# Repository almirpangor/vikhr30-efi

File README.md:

# Вихрь-30 EFI

Блок управления впрыском и зажиганием для лодочного мотора «Вихрь-30» на STM32F103C6T6 (Blue Pill):
программа настройки, прошивка, схема и печатная плата.

| Папка | Что внутри |
|---|---|
| `app/` | Программа настройки 2.0 (TypeScript, React, свой WebGL-движок). `app/desktop/` — оболочка настольного приложения (Electron). Сборка: `node build.mjs`, тесты ядра: `npm test`. |
| `firmware/` | Прошивка v0.9 (исправленная) и v0.8 (для отката), симулятор и тесты на хосте, готовые HEX/BIN в `firmware/release/`. Читать `firmware/README_RU.md`. |
| `pcb/` | Печатная плата rev A: генератор, Gerber и сверловка в `pcb/out/`, файл KiCad, сборочные рисунки, перечень. Читать `pcb/out/README_RU.md`. |
| `release/` | Собранная программа одним HTML-файлом (Chrome/Edge). Установщик для Windows — в разделе Releases. |

## Состояние

Проверено без железа: 24 автотеста ядра программы, 48 проверок прошивки на симуляторе, соответствие Gerber схеме по всем 63 цепям.

**Не проверено на железе:** прошивка v0.9 на настоящем контроллере, программа с настоящим COM-портом,
установщик на Windows, плата (не изготавливалась, файл KiCad в KiCad не открывался), схема из новых деталей.
Перед заказом платы — список «Сверить перед заказом» в `pcb/out/README_RU.md`.

Первые включения — на стенде, с предохранителем и ограничением тока, без топлива. Цепи катушек — до 400 В.

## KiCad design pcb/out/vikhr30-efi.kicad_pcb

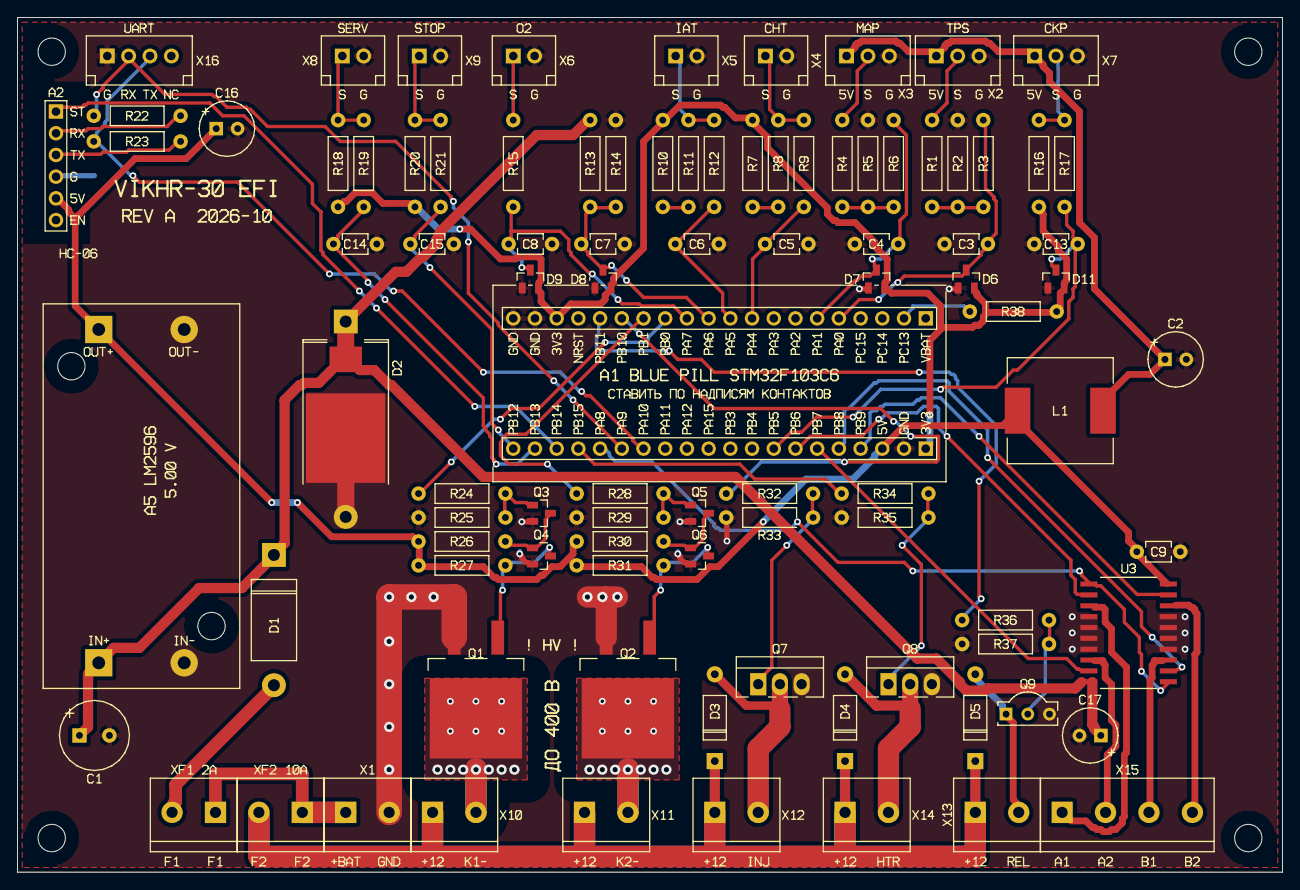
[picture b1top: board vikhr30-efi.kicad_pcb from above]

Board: 2 copper layers, 148.0 x 100.0 mm, 98 parts (0 on the bottom side), 63 nets.

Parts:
A1: Blue Pill STM32F103C6T6; BLUEPILL_2x20
A2: HC-06; HDR_1x6
A5: LM2596S, 5,00 В; LM2596_MODULE
C1: 470 мкФ × 25 В; CP_D8_P3.5
C2, C16, C17: 47 мкФ × 63 В; CP_D6.3_P2.5
C3, C4, C5, C6, C7, C8, C9: 0,1 мкФ; C_DISC_5.08
C13, C14, C15: 1 нФ; C_DISC_5.08
D1: SR560; DO-201AD_15.24
D2: SM8S30A; DO-218AB
D3, D4, D5: 1N4007; DO-41_10.16
D6, D7, D8, D9, D11: BAR43S; SOT-23
H1, H2, H3, H4: M3; MountingHole_3.2mm_M3
L1: 47 мкГн; CDRH125
Q1, Q2: IRGS14C40L; TO-263-2
Q3, Q4, Q5, Q6: AO3400A; SOT-23
Q7, Q8: IRLZ44N; TO-220_V
Q9: BC547C; TO-92
R1, R4, R14, R15, R18, R20, R25, R29, R37, R38: 10 кОм; R_AXIAL_10.16
R2, R5: 20 кОм; R_AXIAL_10.16
R3, R6, R9, R12, R17, R19, R21, R22, R23, R26, R30, R36: 1 кОм; R_AXIAL_10.16
R7, R10: 2,4 кОм; R_AXIAL_10.16
R8, R11: 91 Ом; R_AXIAL_10.16
R13: 47 кОм; R_AXIAL_10.16
R16: 4,7 кОм; R_AXIAL_10.16
R24, R28: 330 Ом; R_AXIAL_10.16
R27, R31: 470 Ом; R_AXIAL_10.16
R32, R34: 100 Ом; R_AXIAL_10.16
R33, R35: 100 кОм; R_AXIAL_10.16
U3: L293DD; SO-20W
X1, X10, X11, X12, X13, X14: Клеммник 2 конт.; TERM_5.08_2
X2, X3, X7: JST XH 3 конт.; JST_XH_3
X4, X5, X6, X8, X9: JST XH 2 конт.; JST_XH_2
X15: JST XH 4 конт.; TERM_5.08_4
X16: JST XH 4 конт. (USB-UART A3); JST_XH_4
XF1: Клеммник 2 конт. к держателю F1 (2 А); TERM_5.08_2R
XF2: Клеммник 2 конт. к держателю F2 (10 А); TERM_5.08_2R

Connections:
+3V3: A1.JL18, A1.JR1, D6.2, D7.2, D8.2, D9.2, D11.2, R7.1, R10.1, R16.1, R18.1, R20.1, R38.1
+5V_ECU: A1.JR3, A2.5, A5.3, C9.1, C16.1, L1.1, R26.1, R27.1, R30.1, R31.1, U3.20
+5V_SENS: C2.1, L1.2, X2.1, X3.1, X7.1
+12V_F2: D3.1, D4.1, D5.1, X10.1, X11.1, X12.1, X13.1, X14.1, XF2.2
+12V_PROT: A5.1, C1.1, C17.1, D1.1, D2.1, R13.1, U3.10
BAT+: X1.1, XF1.1, XF2.1
COIL1-: Q1.2, X10.2
COIL2-: Q2.2, X11.2
GND: A1.JL19, A1.JL20, A1.JR2, A2.4, A5.2, A5.4, C1.2, C2.2, C3.2, C4.2, C5.2, C6.2, C7.2, C8.2, C9.2, C13.2, C14.2, C15.2, C16.2, C17.2, D2.2, D6.1, D7.1, D8.1, D9.1, D11.1, Q1.3, Q2.3, Q3.2, Q4.2, Q5.2, Q6.2, Q7.3, Q8.3, Q9.3, R2.2, R5.2, R14.2, R25.2, R29.2, R33.2, R35.2, R37.2, U3.4, U3.5, U3.6, U3.7, U3.14, U3.15, U3.16, U3.17, X1.2, X2.3, X3.3, X4.2, X5.2, X6.2, X7.3, X8.2, X9.2, X16.1
HEATER-: D4.2, Q8.2, X14.2
IAC_A1: U3.3, X15.1
IAC_A2: U3.8, X15.2
IAC_B1: U3.13, X15.3
IAC_B2: U3.18, X15.4
IGN1_GATE: Q1.1, Q4.3, R27.2
IGN2_GATE: Q2.1, Q6.3, R31.2
INJ-: D3.2, Q7.2, X12.2
MAP_SIG: R4.1, X3.2
N_D1_A: D1.2, XF1.2
N_Q3_1: Q3.1, R24.2, R25.1
N_Q3_3: Q3.3, Q4.1, R26.2
N_Q5_1: Q5.1, R28.2, R29.1
N_Q5_3: Q5.3, Q6.1, R30.2
N_Q7_1: Q7.1, R32.2, R33.1
N_Q8_1: Q8.1, R34.2, R35.1
N_Q9_2: Q9.2, R36.2, R37.1
N_R1_2: R1.2, R2.1, R3.1
N_R4_2: R4.2, R5.1, R6.1
N_R7_2: R7.2, R8.1
N_R10_2: R10.2, R11.1
PA0: A1.JL5, C3.1, D6.3, R3.2
PA1: A1.JL6, C4.1, D7.3, R6.2
PA4: A1.JL9, C5.1, R9.2
PA4_X4: R8.2, R9.1, X4.1
PA5: A1.JL10, C6.1, R12.2
PA5_X5: R11.2, R12.1, X5.1
PA6: A1.JL11, C7.1, D8.3, R13.2, R14.1
PA7: A1.JL12, C8.1, D9.3, R15.2
PA7_X6: R15.1, X6.1
PA8: A1.JR16, U3.1, U3.11
PA9: A1.JR15, R22.1, X16.2
PA9_A2: A2.2, R22.2
PA10: A1.JR14, R23.1, X16.3
PA10_A2: A2.3, R23.2
PB0: A1.JL13, R24.1
PB1: A1.JL14, R28.1
PB5: A1.JR8, C13.1, D11.3, R17.2
PB5_X7: R16.2, R17.1, X7.2
PB6: A1.JR7, U3.2
PB7: A1.JR6, U3.9
PB8: A1.JR5, U3.12
PB9: A1.JR4, U3.19
PB10: A1.JL15, R32.1
PB11: A1.JL16, R36.1
PB12: A1.JR20, C15.1, R21.2
PB12_X9: R20.2, R21.1, X9.1
PB13: A1.JR19, C14.1, R19.2
PB13_X8: R18.2, R19.1, X8.1
PB14: A1.JR18, A2.1
PB15: A1.JR17, R34.1
PC13: A1.JL2, R38.2
RELAY-: D5.2, Q9.1, X13.2
TPS_SIG: R1.1, X2.2

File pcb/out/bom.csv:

Обозначение;Номинал / тип;Корпус (посадочное место);Кол-во;Что купить (строка перечня программы);Ссылка магазина
A1;Blue Pill STM32F103C6T6;BLUEPILL_2x20;1;Плата STM32F103C6T6 (Blue Pill HW-267);https://magazin-elektronika.ru/73-84-23
A2;HC-06;HDR_1x6;1;Bluetooth-модуль HC-06;https://magazin-elektronika.ru/78-00-66
A5;LM2596S, 5,00 В;LM2596_MODULE;1;DC-DC модуль LM2596S (4–40 В → 5 В, 2 А);https://magazin-elektronika.ru/78-96-44
C1;470 мкФ × 25 В;CP_D8_P3.5;1;Конденсатор 470 мкФ × 25 В;https://magazin-elektronika.ru/99-01-97
C2, C16, C17;47 мкФ × 63 В;CP_D6.3_P2.5;3;Конденсатор 47 мкФ × 63 В;https://magazin-elektronika.ru/99-02-36
C3, C4, C5, C6, C7, C8, C9;0,1 мкФ;C_DISC_5.08;7;Конденсатор керамический 0,1 мкФ × 50 В;https://magazin-elektronika.ru/99-00-22
C13, C14, C15;1 нФ;C_DISC_5.08;3;Конденсатор керамический 1 нФ × 50 В;
D1;SR560;DO-201AD_15.24;1;Диод Шоттки SR560 (5 А, 60 В);https://magazin-elektronika.ru/99-42-50
D2;SM8S30A;DO-218AB;1;TVS-диод SM8S30A;https://magazin-elektronika.ru/76-06-46
D3, D4, D5;1N4007;DO-41_10.16;3;Диод 1N4007;https://magazin-elektronika.ru/99-43-56
D6, D7, D8, D9, D11;BAR43S;SOT-23;5;Сборка диодов Шоттки BAR43S (SOT-23);https://magazin-elektronika.ru/76-18-88
L1;47 мкГн;CDRH125;1;Дроссель 47 мкГн, 1,8 А (CDRH125);https://magazin-elektronika.ru/75-99-72
Q1, Q2;IRGS14C40L;TO-263-2;2;IGBT зажигания IRGS14C40L (TO-263);https://magazin-elektronika.ru/99-46-03
Q3, Q4, Q5, Q6;AO3400A;SOT-23;4;MOSFET AO3400A (SOT-23);https://magazin-elektronika.ru/73-20-80
Q7, Q8;IRLZ44N;TO-220_V;2;MOSFET IRLZ44N (TO-220);https://magazin-elektronika.ru/99-46-44
Q9;BC547C;TO-92;1;Транзистор BC547C;https://magazin-elektronika.ru/99-52-75
R1, R4, R14, R15, R18, R20, R25, R29, R37, R38;10 кОм;R_AXIAL_10.16;10;Резисторы 0,25 Вт: 91 Ом, 100 Ом, 330 Ом, 470 Ом, 1 кОм, 2,4 кОм, 4,7 кОм, 10 кОм, 20 кОм, 47 кОм, 100 кОм;https://magazin-elektronika.ru/elektronnye-komponenty/rezistory-13
R2, R5;20 кОм;R_AXIAL_10.16;2;Резисторы 0,25 Вт: 91 Ом, 100 Ом, 330 Ом, 470 Ом, 1 кОм, 2,4 кОм, 4,7 кОм, 10 кОм, 20 кОм, 47 кОм, 100 кОм;https://magazin-elektronika.ru/elektronnye-komponenty/rezistory-13
R3, R6, R9, R12, R17, R19, R21, R22, R23, R26, R30, R36;1 кОм;R_AXIAL_10.16;12;Резисторы 0,25 Вт: 91 Ом, 100 Ом, 330 Ом, 470 Ом, 1 кОм, 2,4 кОм, 4,7 кОм, 10 кОм, 20 кОм, 47 кОм, 100 кОм;https://magazin-elektronika.ru/elektronnye-komponenty/rezistory-13
R7, R10;2,4 кОм;R_AXIAL_10.16;2;Резисторы 0,25 Вт: 91 Ом, 100 Ом, 330 Ом, 470 Ом, 1 кОм, 2,4 кОм, 4,7 кОм, 10 кОм, 20 кОм, 47 кОм, 100 кОм;https://magazin-elektronika.ru/elektronnye-komponenty/rezistory-13
R8, R11;91 Ом;R_AXIAL_10.16;2;Резисторы 0,25 Вт: 91 Ом, 100 Ом, 330 Ом, 470 Ом, 1 кОм, 2,4 кОм, 4,7 кОм, 10 кОм, 20 кОм, 47 кОм, 100 кОм;https://magazin-elektronika.ru/elektronnye-komponenty/rezistory-13
R13;47 кОм;R_AXIAL_10.16;1;Резисторы 0,25 Вт: 91 Ом, 100 Ом, 330 Ом, 470 Ом, 1 кОм, 2,4 кОм, 4,7 кОм, 10 кОм, 20 кОм, 47 кОм, 100 кОм;https://magazin-elektronika.ru/elektronnye-komponenty/rezistory-13
R16;4,7 кОм;R_AXIAL_10.16;1;Резисторы 0,25 Вт: 91 Ом, 100 Ом, 330 Ом, 470 Ом, 1 кОм, 2,4 кОм, 4,7 кОм, 10 кОм, 20 кОм, 47 кОм, 100 кОм;https://magazin-elektronika.ru/elektronnye-komponenty/rezistory-13
R24, R28;330 Ом;R_AXIAL_10.16;2;Резисторы 0,25 Вт: 91 Ом, 100 Ом, 330 Ом, 470 Ом, 1 кОм, 2,4 кОм, 4,7 кОм, 10 кОм, 20 кОм, 47 кОм, 100 кОм;https://magazin-elektronika.ru/elektronnye-komponenty/rezistory-13
R27, R31;470 Ом;R_AXIAL_10.16;2;Резисторы 0,25 Вт: 91 Ом, 100 Ом, 330 Ом, 470 Ом, 1 кОм, 2,4 кОм, 4,7 кОм, 10 кОм, 20 кОм, 47 кОм, 100 кОм;https://magazin-elektronika.ru/elektronnye-komponenty/rezistory-13
R32, R34;100 Ом;R_AXIAL_10.16;2;Резисторы 0,25 Вт: 91 Ом, 100 Ом, 330 Ом, 470 Ом, 1 кОм, 2,4 кОм, 4,7 кОм, 10 кОм, 20 кОм, 47 кОм, 100 кОм;https://magazin-elektronika.ru/elektronnye-komponenty/rezistory-13
R33, R35;100 кОм;R_AXIAL_10.16;2;Резисторы 0,25 Вт: 91 Ом, 100 Ом, 330 Ом, 470 Ом, 1 кОм, 2,4 кОм, 4,7 кОм, 10 кОм, 20 кОм, 47 кОм, 100 кОм;https://magazin-elektronika.ru/elektronnye-komponenty/rezistory-13
U3;L293DD;SO-20W;1;Драйвер L293DD (SO-20);https://magazin-elektronika.ru/99-86-61
X1, X10, X11, X12, X13, X14;Клеммник 2 конт.;TERM_5.08_2;6;Клеммник разъёмный 5,08 мм 2 контакта;https://magazin-elektronika.ru/98-19-50
X2, X3, X7;JST XH 3 конт.;JST_XH_3;3;Набор разъёмов JST XH 2,54 (2–5 контактов);https://magazin-elektronika.ru/74-68-09
X4, X5, X6, X8, X9;JST XH 2 конт.;JST_XH_2;5;Набор разъёмов JST XH 2,54 (2–5 контактов);https://magazin-elektronika.ru/74-68-09
X15;Клеммник 4 конт. 5,08 (на схеме — JST XH 4 конт.);TERM_5.08_4;1;Клеммник разъёмный 5,08 мм — 2 шт. по 2 контакта или один на 4;
X16;JST XH 4 конт. (USB-UART A3);JST_XH_4;1;Набор разъёмов JST XH 2,54 (2–5 контактов);
XF1;Клеммник 2 конт. к держателю F1 (2 А);TERM_5.08_2R;1;Клеммник разъёмный 5,08 мм 2 контакта;
XF2;Клеммник 2 конт. к держателю F2 (10 А);TERM_5.08_2R;1;Клеммник разъёмный 5,08 мм 2 контакта;
—;Гнездо PBS-1x20 под A1;в посадочном месте A1;2;Гнездо PBS-1x20 (или 2 × 1x10), 2,54 мм;https://magazin-elektronika.ru/74-61-86
—;Гнездо PBS-1x6 под A2 (HC-06);HDR_1x6;1;из линейки PBS, 2,54 мм;
—;Стойки М3 для модуля A5 и крепежа платы;;6;;

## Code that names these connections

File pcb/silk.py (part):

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}
CONN_NAME = {'X2': 'TPS', 'X3': 'MAP', 'X4': 'CHT', 'X5': 'IAT', 'X6': 'O2', 'X7': 'CKP', 'X8': 'SERV', 'X9': 'STOP', 'X16': 'UART'}
REF_TEXT = {'XF1': 'XF1 2A', 'XF2': 'XF2 10A'}
MCU = {**{f'JL{i + 1}': n for i, n in enumerate('VBAT PC13 PC14 PC15 PA0 PA1 PA2 PA3 PA4 PA5 PA6 PA7 PB0 PB1 PB10 PB11 NRST 3V3 GND GND'.split())},
       **{f'JR{i + 1}': n for i, n in enumerate('3V3 GND 5V PB9 PB8 PB7 PB6 PB5 PB4 PB3 PA15 PA12 PA11 PA10 PA9 PA8 PB15 PB14 PB13 PB12'.split())}}

def pad_shape(p, layer='T'):
    s = [q for q in B.shapes_of_pad(p) if q.layer == layer]
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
